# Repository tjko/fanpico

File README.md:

# Fanpico: Programmable PWM (PC) Fan Controller

<p></p>

Fanpico is a smart PWM (PC) fan controller based around [Raspberry Pi Pico](https://www.raspberrypi.com/documentation/microcontrollers/raspberry-pi-pico.html) (RP2040 MCU). Fanpico operates as standalone controller that can be configured and left running. It does not require any drivers and doesn't care what OS is being used. FanPico is an Open-source hardware (OSHW) project.

## What is it for?
* Fanpico is for customizing fan "curves" to fine tune how your motherboard controlled fans run.
* Fine tuning fan speeds to easily balance airflow.
* Controlling fan based on temperature sensor input.
* Monitoring fan speeds and behaviour as well as monitoring what exactly motherboard is doing.
* Fanpico works also as standalong controller for other things than a PC, it's been used  controlling fans on 3D printers and on enclosed network equipment racks, etc..

## Features
* Controls up to 8 fans.
* Connect up to 4 motherboard fan outputs.
* Connect up to 2 remote temperature probes (plus onboard "ambient" temperature sensor).
* Support for [1-Wire Temperature sensors](https://github.com/tjko/fanpico/wiki/1%E2%80%90Wire-Temperature-Sensors-with-FanPico) (up to 8 sensors)
* Support for [I2C Temperature sensors](https://github.com/tjko/fanpico/wiki/I2C-Temperature-Sensors-with-FanPico) (up to 8 sensors)
* [OLED](https://github.com/tjko/fanpico/wiki/OLED-(I2C)-Display-Support) and [LCD](https://github.com/tjko/fanpico/wiki/LCD-(SPI)-Panel-Connection) display support (boards where model name ends with "D").
* Can be powered from motherboard fan outputs or using auxiliary power connector (4-Pin Floppy or DC Barrel jack connector).
* Ability to define custom fan "curves" for each fan.
* Ability to provide custom tachometer (fan RPM) output signal back to motherboard.
* Support for Locked Rotor (Alarm) signal fans (allows using regular tachometer fans with system expecting Locked Rotor Alarm fans and vice versa).
* Control fans from any motherboard PWM signal or from temperature sensors.
* OS Independent, no drivers or software needed.
* Configuration stored on the device itself (in the flash memory).
* SCPI "like" programming interface (see [Command Reference](commands.md))
* Monitor each fan and motherboard output signals as well as temperatures.
* [WiFi support](https://github.com/tjko/fanpico/wiki/FanPico-Network-Interface) if opting to mount Pico W on the board.
  * [HTTP server](https://github.com/tjko/fanpico/wiki/Fanpico-HTTP-Server) with TLS (HTTPS) support.
  * [MQTT client](https://github.com/tjko/fanpico/wiki/FanPico-MQTT-Tutorial) with TLS support for logging data and to receive commands.
  * [Home Assistant](https://github.com/tjko/fanpico/wiki/FanPico-Home-Assistant-(MQTT-Discovery)-Support) support using MQTT Discovery feature.
  * Telnet server for configuration and monitoring.
  * [SSH server](https://github.com/tjko/fanpico/wiki/Fanpico-Using-SSH-Server) for configuration and monitoring (experimental).
  * [SNMP Agent](https://github.com/tjko/fanpico/wiki/SNMP-Agent-Usage) for monitoring.

### Interfaces

* Serial "Console". Primary method for configuring/monitoring FanPico units is via (USB) Serial console (some units also have 3.3V TTL Serial connection).
* Desktop application (that polls FanPico using SCPI commands over the console connection): [FanPico Monitor](https://github.com/tjko/fanpico-monitor)
* Web Interface (available when using _Pico W_) over WiFi

For more documentation check [FanPico Wiki](https://github.com/tjko/fanpico/wiki)

## Sponsors
I would like to thank following sponsors, who have helped FanPico project:

* PCBWay

## Where can I get one?
Currently Fanpico is available as a DIY project.
Check discussion forums for places to purchase Kits or PCBs: [Places to Purchase FanPico](https://github.com/tjko/fanpico/discussions/12)

(Instructions for building the kit are in [FanPico Wiki](https://github.com/tjko/fanpico/wiki))

However, if there is sufficient interest, then ready-made units may be made available for sale.
If you'd be interested in purchasing FanPico pease indicate your interest here: [FanPico Forum](https://github.com/tjko/fanpico/discussions/9)

### DIY Option
You can upload the Kerber files (found under boards directory) to your favorite PCB maker website and get your boards produced in matter of days.
Component list (BOM or bill of materials) is found under boards directory as well along with the electrical schematics.

NOTE, check [discussions forum](https://github.com/tjko/fanpico/discussions/) for giveaways for free PCBs.

### Review Units
If you are member of press (or YouTuber) and would like to review/test Fanpico. Please contact me via email.

## How Can I help?
* Build your own FanPico and provide feedback, suggestions (see discussion forums).
* If you're into electronics new/improved board designs are most welcome.
* If you're into programming:
  - Create cool (desktop) program that allows easily configuring FanPico boards (with ability to "draw" fan curves, etc..) and to monitor Fan statuses.
  - Help improve the firmware.
* If you're into graphics (or web) design:
  - Help create cool (but lightweight) web interface
  - Create better logo for FanPico
* As this is Open (Source) Hardware Project, if you like to build (and sell) assembled boards or DIY kits, you'd be most welcome...
* You can always donate (and get your name added to the Sponsors section, if you so wish).

## Hardware
Fanpico is Open Source Hardware, reference design is provided for the "0804" model (8 fan outputs and 4 motherboard fan inputs), and "0804D" model that adds OLED display support (hence the "D" suffix).

Additional models with different combinations of fan inputs/outputs could be easily designed (takining into account limitations of Raspberry Pi Pico I/O limits). New and improved PCB models/designs are most welcome.

Model "0840D" with (with right-angle connectors and DC power connector):

Model "0804" without display (with straight connectors):

### Hardware Design
Fanpico (reference design) utilizes all available I/O pins on a Raspberry Pi Pico.
* Fan PWM outputs are driven by the Pico's PWM hardware.
* Motherboard Fan PWM inputs are read using Pico's PWM hardware.
* Tacho signal output (for motherboard connectors) is generated using Pico's PIO hardware, providing extremely stable tachometer signal.
* Tacho signal inputs (from fans) are read differently in model 0804 and 0804D:
  - 0804: signals are read using GPIO interrupts, measuring all fans simultaneously by counting number of pulses received over a period of time.
  - 0804D: signals are read through multiplexer measuring one fan at a time, by measuring pulse length.
* Temperature readings are done using ADC, with help of a accurrate 3V voltage reference (LM4040). Any NTC (10k or 100k) thermistors can be used as themperature sensors.
* Each FAN output has jumper to select whether fan gets its power from associated MBFAN connector or from the AUX connector
* There is a jumper to select whether power the Fanpico itself from MBFAN1 or AUX connector.

To help design and test Fanpico couple other projects were born:
* [Tiny PicoProbe](https://github.com/tjko/tiny-picoprobe/) - tiny PicoProbe implementation.
* [Fan Test Adapter](https://github.com/tjko/fan-test-adapter/) - adapter to help simulate motherboard fan outputs.

Projects based on FanPico firmware:
* [BrickPico](https://github.com/tjko/brickpico/) - (LEGO) LED Light Kit Controller.

### Models (PCB designs)
Currently following models are available:

|Model|Fans (Outputs)|MB Fan (Inputs)|External Temperature Sensors|Display|Notes|
|-----|--------------|---------------|-------------------|--------|-----|
|[FANPICO-0804](boards/fanpico-0804/)|8|4|2|N|First publicly available board (reference design).|
|[FANPICO-0804D](boards/fanpico-0804D/)|8|4|2|Y|Support for OLED (128x64 or 128x128) displays|
|[FANPICO-0401D](boards/fanpico-0401D/)|4|1|2|Y|Adds QWIIC and 1-Wire connectors.|
|[FANPICO-0200](boards/fanpico-0200/)|2|0|2|Y|OLED display supported via QWIIC connector. PCB under development.

(all boards have one additional 'on-board' temperature sensor on the RP2040 MCU itself)

Models ending with "D" have connector to attach OLED display module to see 'real-time' status of fans and temperatures.

OLED panel directly mounted on the PCB:

LCD Panel attached via a short cable:

#### Accessory Boards (PCB designs)
Following accessories are available:

|Model|Info|
|-----|----|
|[OLED-Adapter](boards/oled-adapter/)|Mounting adapter for OLED boards with different pinouts.|
|[Power-Board](boards/power-board/)|Adapter for using high-power fans with FanPico.|

## Firmware
Firmware is developed in C using the Pico SDK. Pre-compiled firmware is released when there is new major features or bug fixes.

Latest pre-compiled firmware image can be found here: [Releases](https://github.com/tjko/fanpico/releases)

To get latest firmware with latest updates/fixes you must compile the firmware from the sources.

### Installing firmware image
Firmware can be installed via the built-in UF2 bootloader on the Raspberry Pi Pico or using the debug header with Picoprobe, etc...

#### Selecting Right Firmware to use
Each release (zip file) contains multiple different firmware files.
Make sure to select firmware for the board you're using and for the pico model ("pico_w" if using Pico W).

Firmware file names have format: fanpico-<board_model>-<pico_model>.uf2
```
fanpico-0401D-pico.uf2
fanpico-0401D-pico_w.uf2
fanpico-0804-pico.uf2
fanpico-0804-pico_w.uf2
fanpico-0804D-pico.uf2
fanpico-0804D-pico_w.uf2
```

#### Upgrading Firmware
Firmware upgrade steps:
* Boot Pico into UF2 bootloader. This can be done in two ways:
  1)  Press and hold "bootsel" button and then press and release "reset" button.
  2)  Issue command: SYS:UPGRADE
* Copy firmware file to the USB mass storage device that appears.
* As soon as firmware copy is complete, Pico will reboot and run the fanpico firmware.

### Building Firmware Images

Raspberry Pi Pico C/C++ SDK is required for compiling the firmware:

#### Requirements / Dependencies
* [Raspberry Pi Pico C/C++ SDK](https://www.raspberrypi.com/documentation/microcontrollers/c_sdk.html)
* [cJSON](https://github.com/DaveGamble/cJSON)
* [pico-lfs](https://github.com/tjko/pico-lfs)
* [ss_oled-lib](https://github.com/tjko/ss_oled-lib)
* [bb_spi_lcd-lib](https://github.com/tjko/bb_spi_lcd-lib)
* [libb64](https://github.com/libb64/libb64)
* [pico-telnetd](https://github.com/tjko/pico-telnetd)
* [pico-1wire-lib](https://github.com/tjko/pico-1wire-lib)
* [pico-sensor-lib](https://github.com/tjko/pico-sensor-lib)
* [wolfSSL](https://github.com/wolfSSL/wolfssl)
* [wolfSSH](https://github.com/wolfSSL/wolfssh)
* [pico-sshd](https://github.com/tjko/pico-sshd)

##### Install Pico SDK
Pico SDK must be installed working before you can compile fanpico.

Instructions on installing Pico SDK see: [Getting started with Raspberry Pi Pico](https://datasheets.raspberrypi.com/pico/getting-started-with-pico.pdf)

(Make sure PICO_SDK_PATH environment variable is set)

##### Downloading sources

Create some directory for building fanpico ('src' used in this example):
```
$ mkdir src
$ cd src
$ git clone https://github.com/tjko/fanpico.git
$ git submodule update --init --recursive
```

##### Building fanpico firmware

To build fanpico firmware, first create a build directory:
```
$ cd fanpico
$ mkdir build
```

Select which board to build firmware for (default is "0804") and which Pico is to be used (default is "pico"):
```
$ cd build
$ cmake -DFANPICO_BOARD=0804D -DPICO_BOARD=pico_w ..
```

Then compile fanpico:
```
$ make -j
```

After successful compile you should see firmware binary in the build directory:
subdirectory:

```
$ ls *.uf2
fanpico.uf2
```

If you have picotool installed you can check the firmware image information:
```
$ picotool info -a fanpico.uf2
File fanpico.uf2 family ID 'rp2040':

Program Information
 name:              fanpico
 version:           1.7.6
 web site:          https://kokkonen.net/fanpico/
 description:       FanPico-0804D - Smart PWM Fan Controller
 features:          USB stdin / stdout
 boot settings:     bootdelay = 0
                    safemode = 0
 binary start:      0x10000000
 binary end:        0x1012edc0
 embedded drive:    0x101c0000-0x10200000 (256K): littlefs

Fixed Pin Information
 0:                 TX (Serial) / MISO (SPI)
 1:                 RX (Serial) / CS (SPI)
 2:                 SDA (I2C) / SCK (SPI)
 3:                 SCL (I2C) / MOSI (SPI)
 4:                 Fan1 PWM signal (output)
 5:                 Fan2 PWM signal (output)
 6:                 Fan3 PWM signal (output)
 7:                 Fan4 PWM signal (output)
 8:                 Fan5 PWM signal (output)
 9:                 Fan6 PWM signal (output)
 10:                Fan7 PWM signal (output)
 11:                Fan8 PWM signal (output)
 12:                MB Fan1 tacho signal (output)
 13:                MB Fan1 PWM signal (input)
 14:                MB Fan2 tacho signal (output)
 15:                MB Fan2 PWM signal (input)
 16:                MB Fan3 tacho signal (output)
 17:                MB Fan3 PWM signal (input)
 18:                MB Fan4 tacho signal (output)
 19:                MB Fan4 PWM signal (input)
 20:                Multiplexer S2 (output)
 21:                Multiplexer S1 (output)
 22:                Multiplexer S0 (output)
 26:                Multiplexer A [tacho signal] (input)
 27:                Temperature Sensor1 (input)
 28:                Temperature Sensor2 (input)

Build Information
 sdk version:       2.1.1
 pico_board:        pico_w
 boot2_name:        boot2_w25q080
 build date:        Jul 10 2025
 build attributes:  Release

Metadata Blocks
 none
```

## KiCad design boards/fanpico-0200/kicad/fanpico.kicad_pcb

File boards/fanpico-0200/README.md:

# FANPICO-0200 PCB

PCB Size: 81.0mm x 60.0mm

## Change Log

v1.1
- Add fuse (F3) to prevent pulling too much current through the buck regulator.
- Move sensor connectors footprints (J16 & J17) slightly away from board edge
  to allow better fitment of right angle connectors.

v1.0
- First Prototye

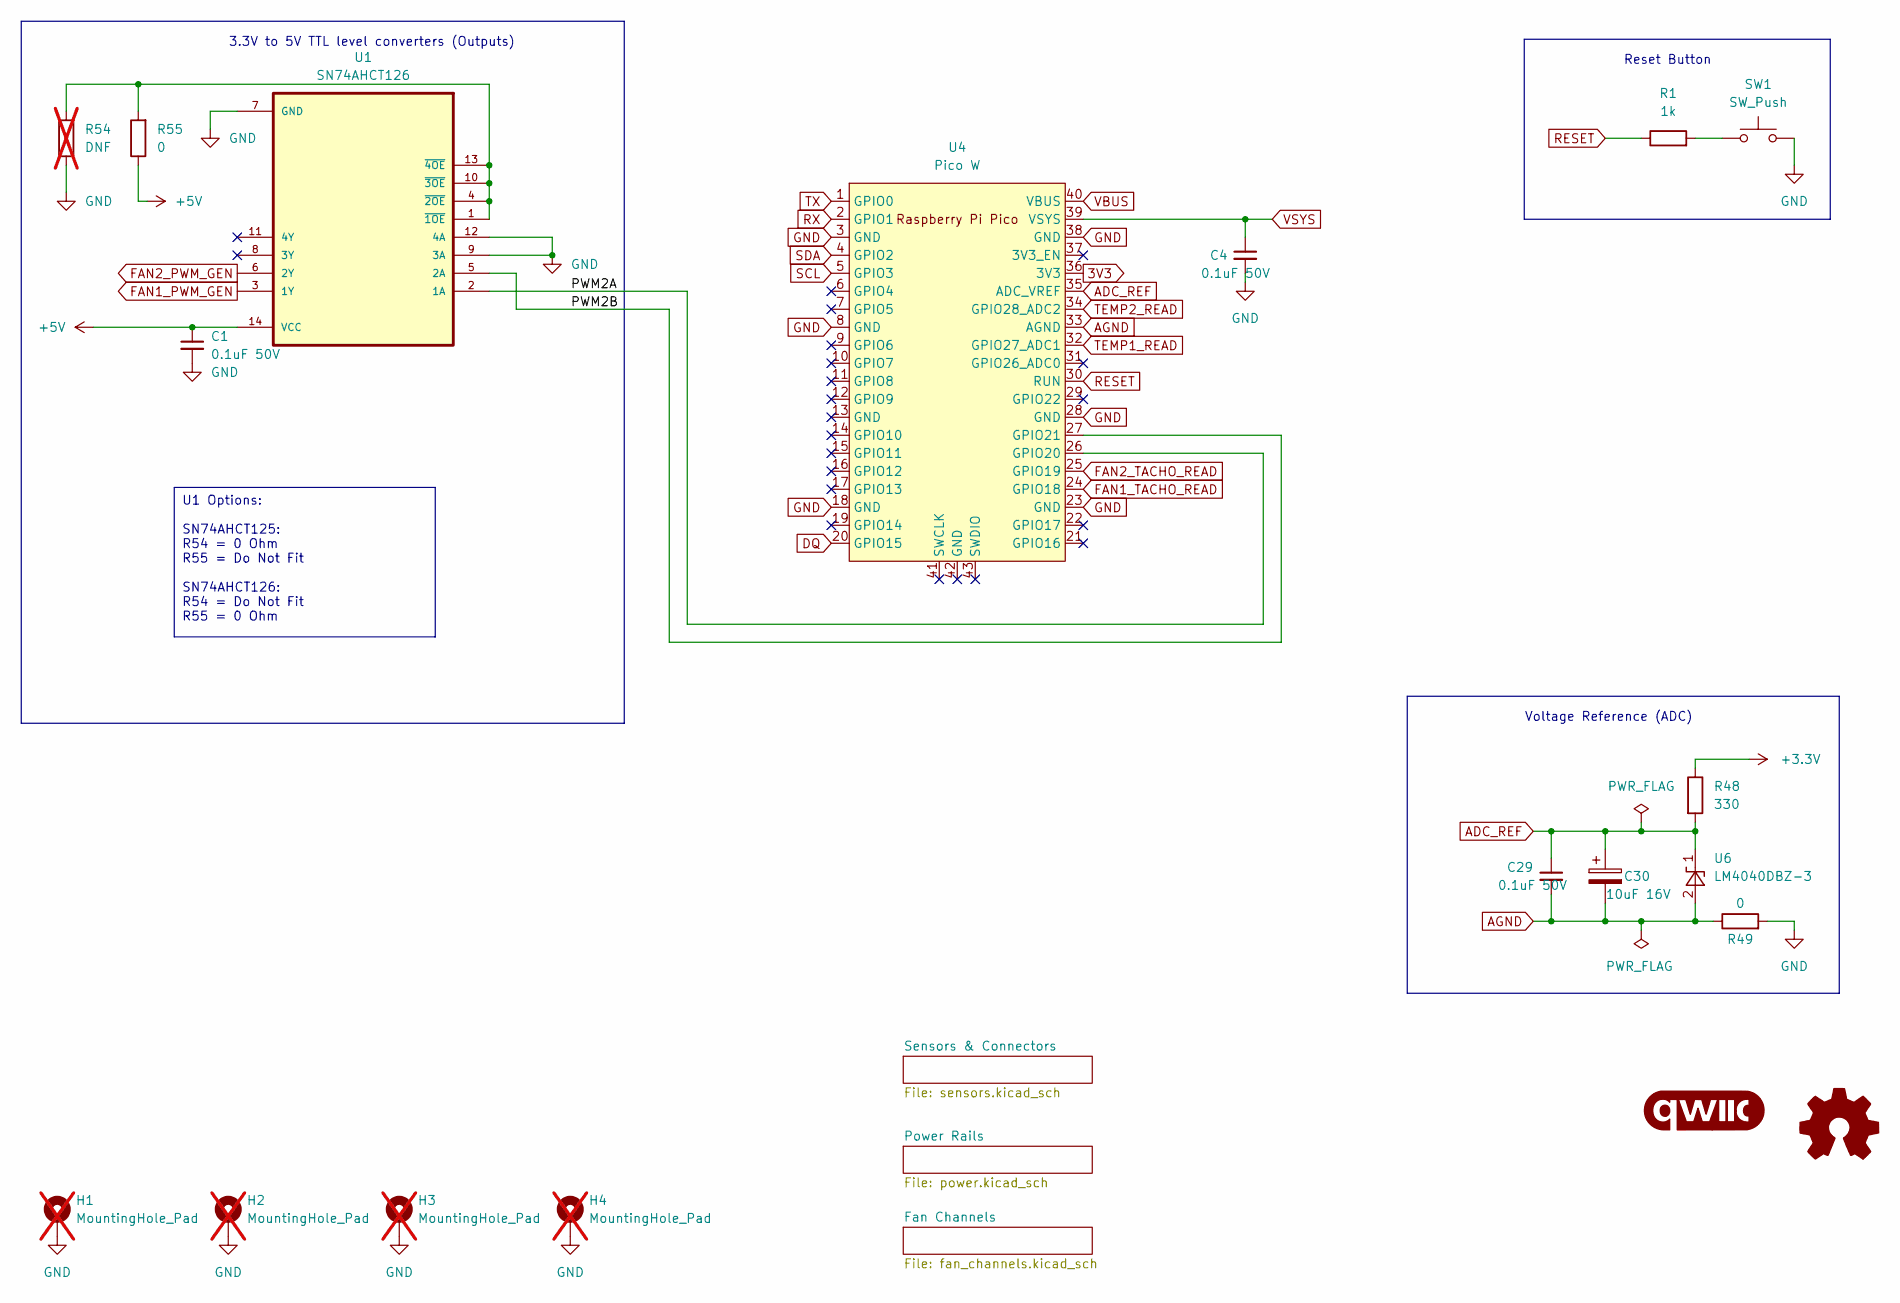
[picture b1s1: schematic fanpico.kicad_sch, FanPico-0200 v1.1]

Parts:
C1, C4, C29: 0.1uF 50V; C_0603_1608Metric_Pad1.08x0.95mm_HandSolder; Manufacturer Part Number CL10B104KB8NNNC; LCSC Part Number C1591
C30: 10uF 16V; CP_EIA-3216-18_Kemet-A_Pad1.58x1.35mm_HandSolder; Mouser Part Number 80--T491A106K016; LCSC Part Number C7171
G1: qwiic_Logo; qwiic_5mm
G2: Logo_Open_Hardware_Small; OSHW-Logo_5.7x6mm_SilkScreen
H1, H2, H3, H4: MountingHole_Pad; MountingHole_3.2mm_M3_Pad_Via; not fitted
R1: 1k; R_0603_1608Metric_Pad0.98x0.95mm_HandSolder; Manufacturer Part Number RC0603FR-071KL; LCSC Part Number C22548
R48: 330; R_0603_1608Metric_Pad0.98x0.95mm_HandSolder; Manufacturer Part Number RC0603FR-07330RL; LCSC Part Number C105881
R49, R55: 0; R_0603_1608Metric_Pad0.98x0.95mm_HandSolder; Manufacturer Part Number 0603WAF0000T5E; LCSC Part Number C21189
R54: DNF; R_0603_1608Metric_Pad0.98x0.95mm_HandSolder; Manufacturer Part Number 0603WAF0000T5E; LCSC Part Number C21189; not fitted
SW1: SW_Push; SW-SMD_L3.9-W3.0-P4.45; Manufacturer Part Number TS-1088-AR02016; LCSC Part Number C720477
U1: SN74AHCT126; TSSOP-14_4.4x5mm_P0.65mm; Manufacturer Part Number SN74AHCT126PWR; LCSC Part Number C155177
U4: Pico W; RPi_Pico_PicoW_SMD_TH; Manufacturer Part Number Pico W / Pico 2 W
U6: LM4040DBZ-3; SOT-23; Manufacturer Part Number LM4040AIM3-3.0+T; LCSC Part Number C143326

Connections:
3V3: R48.1, U4.36 (3V3); also elsewhere on the board
+5V: C1.1, R55.1, U1.14 (VCC); also elsewhere on the board
/PWM2A: U1.2 (1A), U4.26 (GPIO20)
/PWM2B: U1.5 (2A), U4.27 (GPIO21)
ADC_REF: C29.1, C30.1, R48.2, U4.35 (ADC_VREF), U6.1 (K); also elsewhere on the board
AGND: C29.2, C30.2, R49.1, U4.33 (AGND), U6.2 (A); also elsewhere on the board
DQ: U4.20 (GPIO15); also elsewhere on the board
FAN1_PWM_GEN: U1.3 (1Y); also elsewhere on the board
FAN1_TACHO_READ: U4.24 (GPIO18); also elsewhere on the board
FAN2_PWM_GEN: U1.6 (2Y); also elsewhere on the board
FAN2_TACHO_READ: U4.25 (GPIO19); also elsewhere on the board
GND: C1.2, C4.2, H1.1, H2.1, H3.1, H4.1, R49.2, R54.1, SW1.2, U1.7 (GND), U1.9 (3A), U1.12 (4A), U4.3 (GND), U4.8 (GND), U4.18 (GND), U4.23 (GND), U4.28 (GND), U4.38 (GND); also elsewhere on the board
unnamed: R1.2, SW1.1
unnamed: R54.2, R55.2, U1.1 (~1OE), U1.4 (~2OE), U1.10 (~3OE), U1.13 (~4OE)
RESET: R1.1, U4.30 (RUN)
RX: U4.2 (GPIO1); also elsewhere on the board
SCL: U4.5 (GPIO3); also elsewhere on the board
SDA: U4.4 (GPIO2); also elsewhere on the board
TEMP1_READ: U4.32 (GPIO27_ADC1); also elsewhere on the board
TEMP2_READ: U4.34 (GPIO28_ADC2); also elsewhere on the board
TX: U4.1 (GPIO0); also elsewhere on the board
VBUS: U4.40 (VBUS); also elsewhere on the board
VSYS: C4.1, U4.39 (VSYS); also elsewhere on the board

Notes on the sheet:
U1 Options: SN74AHCT125: R54 = 0 Ohm R55 = Do Not Fit SN74AHCT126: R54 = Do Not Fit R55 = 0 Ohm
Reset Button
3.3V to 5V TTL level converters (Outputs)
Voltage Reference (ADC)

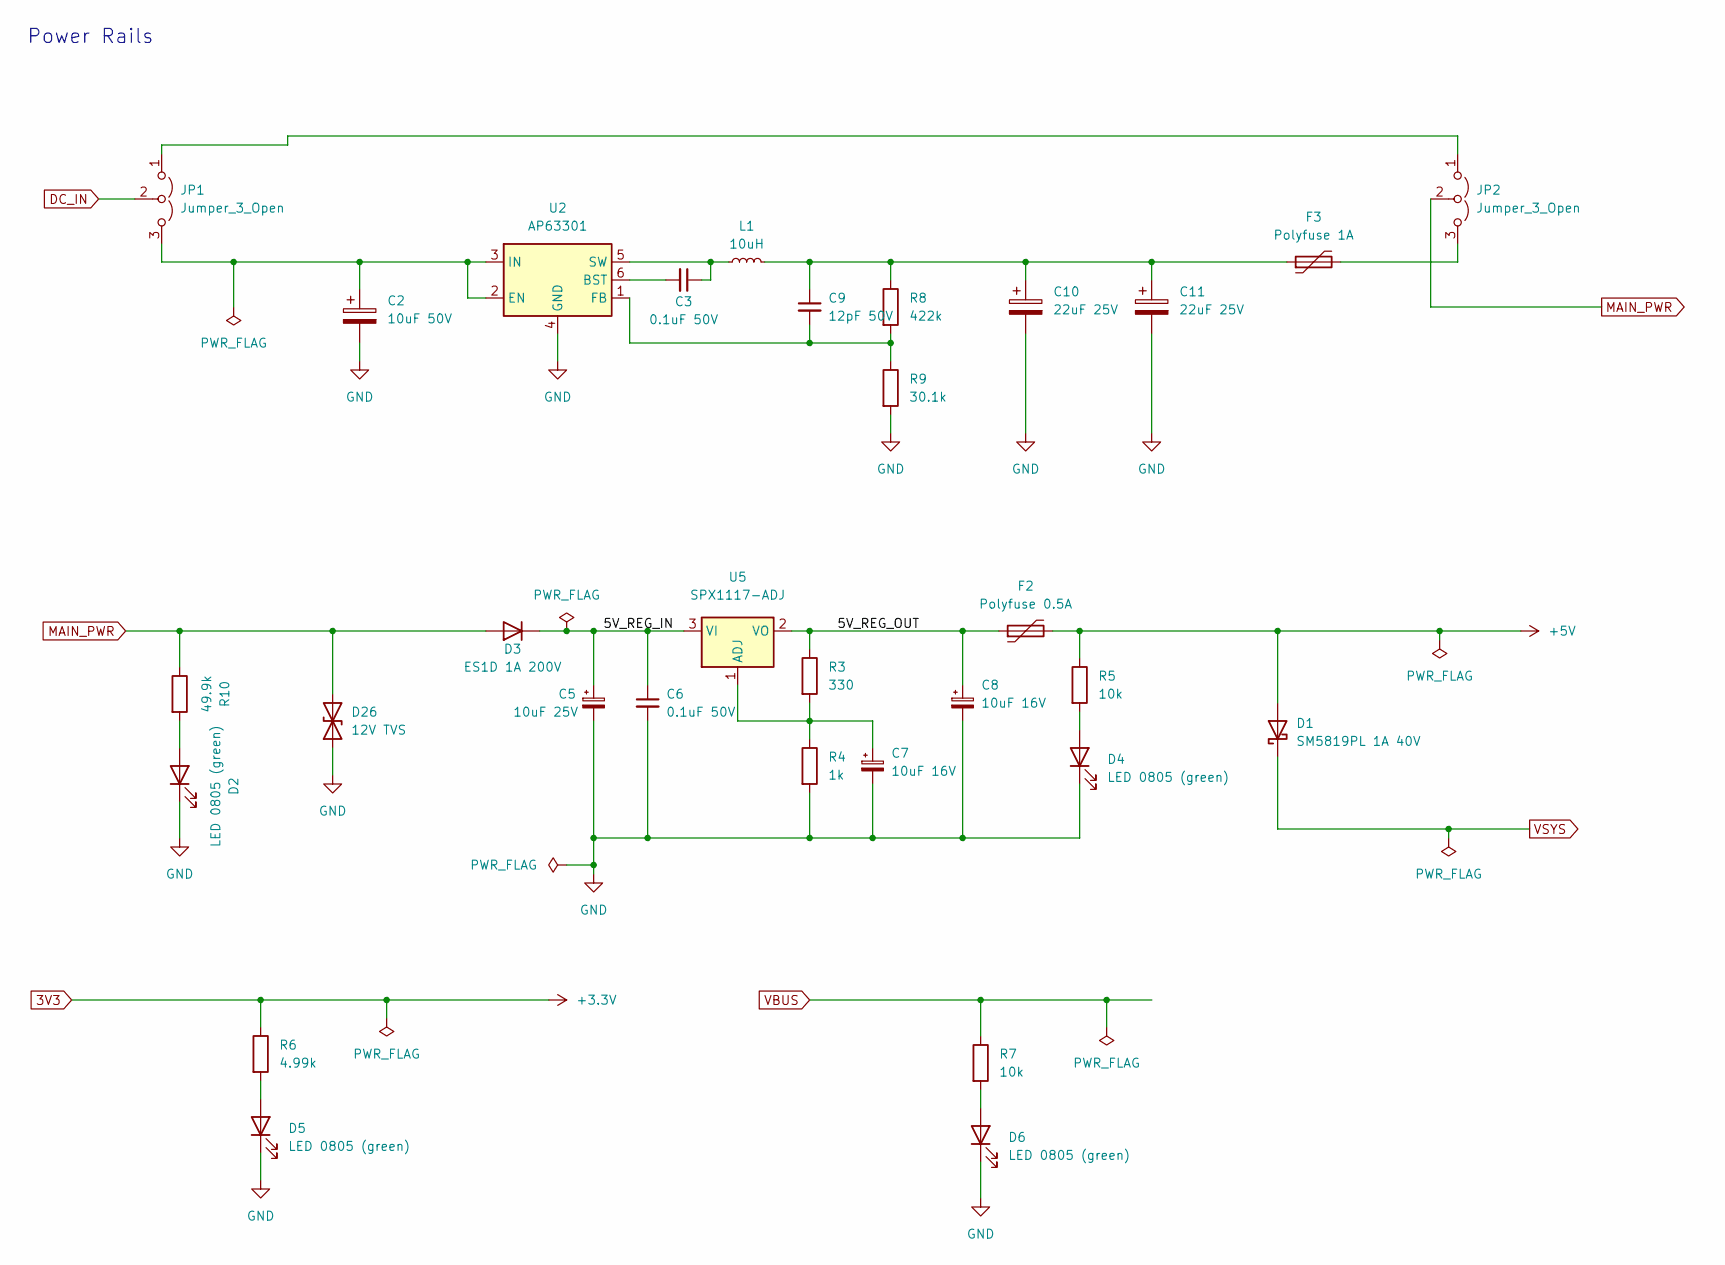
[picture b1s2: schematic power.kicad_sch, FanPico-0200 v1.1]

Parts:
C2: 10uF 50V; CP_EIA-3216-18_Kemet-A_Pad1.58x1.35mm_HandSolder; Manufacturer Part Number CL31B106KBHNNNE; LCSC Part Number C89632
C3, C6: 0.1uF 50V; C_0603_1608Metric_Pad1.08x0.95mm_HandSolder; Manufacturer Part Number CL10B104KB8NNNC; LCSC Part Number C1591
C5: 10uF 25V; CP_EIA-3528-12_Kemet-T_Pad1.50x2.35mm_HandSolder; Manufacturer Part Number TAJB106K025RNJ; LCSC Part Number C7194
C7, C8: 10uF 16V; CP_EIA-3216-18_Kemet-A_Pad1.58x1.35mm_HandSolder; Mouser Part Number 80--T491A106K016; LCSC Part Number C7171
C9: 12pF 50V; C_0603_1608Metric_Pad1.08x0.95mm_HandSolder; Manufacturer Part Number CL10C120JB8NNNC; LCSC Part Number C38523
C10, C11: 22uF 25V; CP_EIA-3216-18_Kemet-A_Pad1.58x1.35mm_HandSolder; Manufacturer Part Number CL31A226KAHNNNE; LCSC Part Number C12891
D1: SM5819PL 1A 40V; D_SMA; Mouser Part Number 833-SM5819PL-TP; LCSC Part Number C669023
D2, D4, D5, D6: LED 0805 (green); LED_0805_2012Metric_Pad1.15x1.40mm_HandSolder; Mouser Part Number 710-150080GS75000; LCSC Part Number C434432
D3: ES1D 1A 200V; D_SMA_Handsoldering; Mouser Part Number 512-ES1D; LCSC Part Number C445494
D26: 12V TVS; D_SOD-323_HandSoldering; Manufacturer Part Number UDD32C12L01-ES; LCSC Part Number C5199168
F2: Polyfuse 0.5A; Fuse_1206_3216Metric_Pad1.42x1.75mm_HandSolder; Mouser Part Number 530-0ZCJ0050AF2E; LCSC Part Number C70072
F3: Polyfuse 1A; Fuse_1206_3216Metric_Pad1.42x1.75mm_HandSolder; Manufacturer Part Number 1206L100/30NR; LCSC Part Number C7542958
JP1, JP2: Jumper_3_Open; PinHeader_1x03_P2.54mm_Vertical; Manufacturer Part Number PZ254V-11-03P; LCSC Part Number C2937625
L1: 10uH; IND-SMD_L7.2-W6.6_GPSR07X0; Manufacturer Part Number CYA0630-10UH; LCSC Part Number C5189958
R3: 330; R_0603_1608Metric_Pad0.98x0.95mm_HandSolder; Manufacturer Part Number RC0603FR-07330RL; LCSC Part Number C105881
R4: 1k; R_0603_1608Metric_Pad0.98x0.95mm_HandSolder; Manufacturer Part Number RC0603FR-071KL; LCSC Part Number C22548
R5, R7: 10k; R_0603_1608Metric_Pad0.98x0.95mm_HandSolder; Manufacturer Part Number RC0603FR-0710KL; LCSC Part Number C98220
R6: 4.99k; R_0603_1608Metric_Pad0.98x0.95mm_HandSolder; Manufacturer Part Number RC0603FR-074K99L; LCSC Part Number C114621
R8: 422k; R_0603_1608Metric_Pad0.98x0.95mm_HandSolder; Manufacturer Part Number RC0603FR-07422KL; LCSC Part Number C245966
R9: 30.1k; R_0603_1608Metric_Pad0.98x0.95mm_HandSolder; Manufacturer Part Number 0603WAF3012T5E; LCSC Part Number C23000
R10: 49.9k; R_0603_1608Metric_Pad0.98x0.95mm_HandSolder; Manufacturer Part Number RC0603FR-0749K9L; LCSC Part Number C114624
U2: AP63301; TSOT-26; Manufacturer Part Number AP63301WU-7; LCSC Part Number C2158003
U5: SPX1117-ADJ; SOT-223-3_TabPin2; Manufacturer Part Number SPX1117M3-L/TR; LCSC Part Number C67402

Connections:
3V3: R6.1; also elsewhere on the board
+5V: D1.2 (A), F2.2, R5.1; also elsewhere on the board
/Power Rails/5V_REG_IN: C5.1, C6.1, D3.1 (K), U5.3 (VI)
/Power Rails/5V_REG_OUT: C8.1, F2.1, R3.1, U5.2 (VO)
DC_IN: JP1.2 (C); also elsewhere on the board
GND: C2.2, C5.2, C6.2, C7.2, C8.2, C10.2, C11.2, D2.1 (K), D4.1 (K), D5.1 (K), D6.1 (K), D26.1 (A1), R4.2, R9.2, U2.4 (GND); also elsewhere on the board
MAIN_PWR: D3.2 (A), D26.2 (A2), JP2.2 (C), R10.1; also elsewhere on the board
unnamed: C9.1, C10.1, C11.1, F3.1, L1.2, R8.1
unnamed: D2.2 (A), R10.2
unnamed: D4.2 (A), R5.2
unnamed: D5.2 (A), R6.2
unnamed: D6.2 (A), R7.2
unnamed: JP1.1 (A), JP2.1 (A)
unnamed: C2.1, JP1.3 (B), U2.2 (EN), U2.3 (IN)
unnamed: F3.2, JP2.3 (B)
unnamed: C3.2, U2.6 (BST)
unnamed: C9.2, R8.2, R9.1, U2.1 (FB)
unnamed: C3.1, L1.1, U2.5 (SW)
unnamed: C7.1, R3.2, R4.1, U5.1 (ADJ)
VBUS: R7.1; also elsewhere on the board
VSYS: D1.1 (K); also elsewhere on the board

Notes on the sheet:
Power Rails

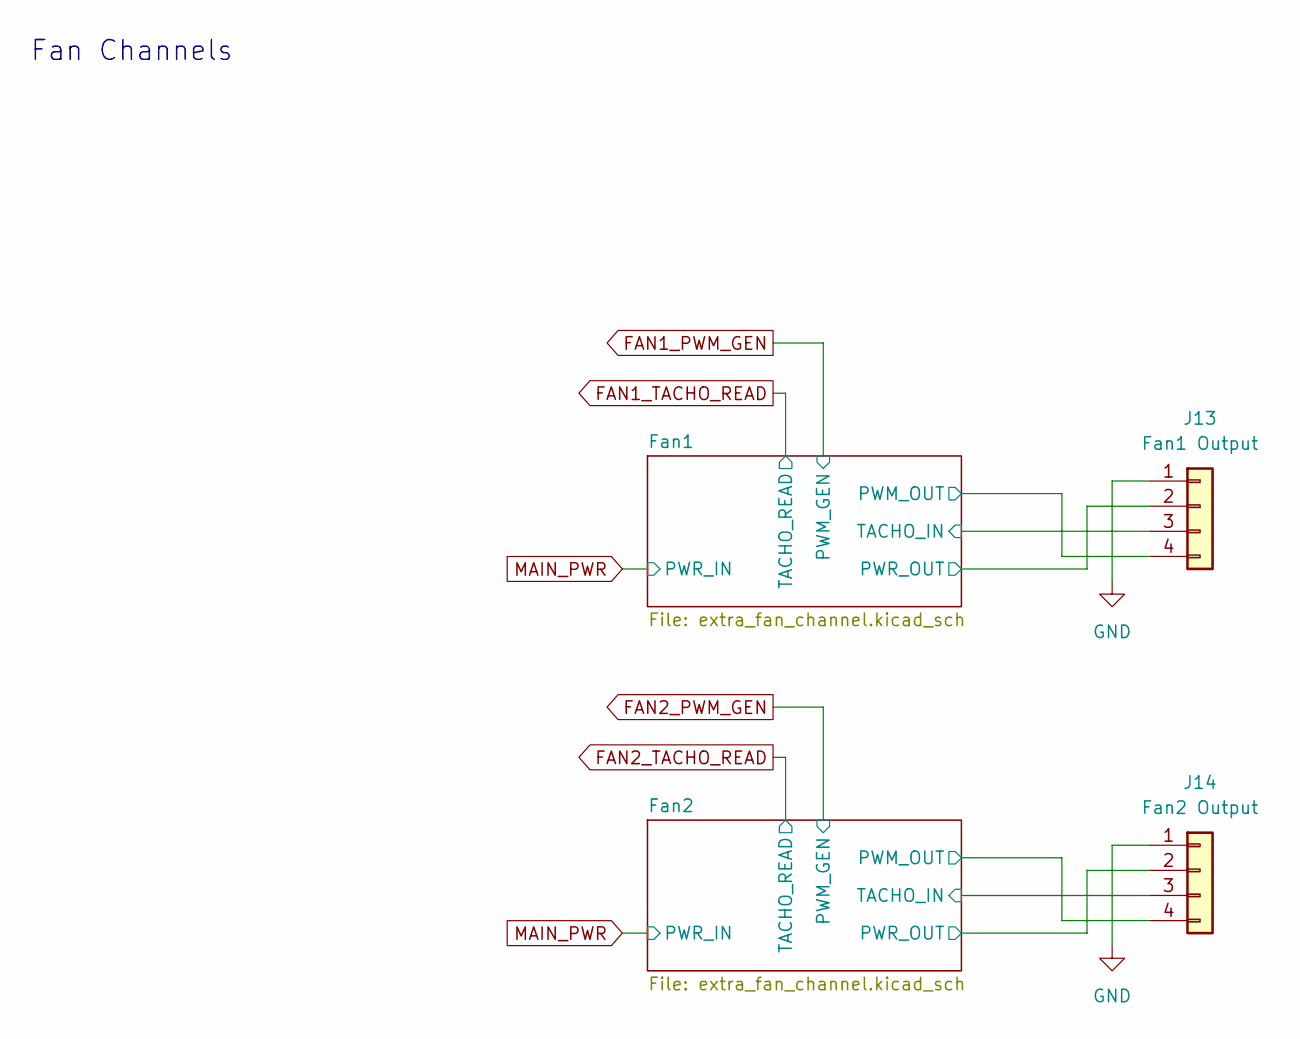
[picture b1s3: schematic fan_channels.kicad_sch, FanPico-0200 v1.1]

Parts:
J13: Fan1 Output; FanPinHeader_1x04_P2.54mm_Vertical; Mouser Part Number 538-47053-1000; LCSC Part Number C240840
J14: Fan2 Output; FanPinHeader_1x04_P2.54mm_Vertical; Mouser Part Number 538-47053-1000; LCSC Part Number C240840

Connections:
/Fan Channels/Fan1/PWM_OUT: J13.4; also elsewhere on the board
/Fan Channels/Fan1/TACHO_IN: J13.3; also elsewhere on the board
/Fan Channels/Fan2/PWM_OUT: J14.4; also elsewhere on the board
/Fan Channels/Fan2/TACHO_IN: J14.3; also elsewhere on the board
GND: J13.1, J14.1; also elsewhere on the board
MAIN_PWR: J13.2, J14.2; also elsewhere on the board

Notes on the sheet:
Fan Channels

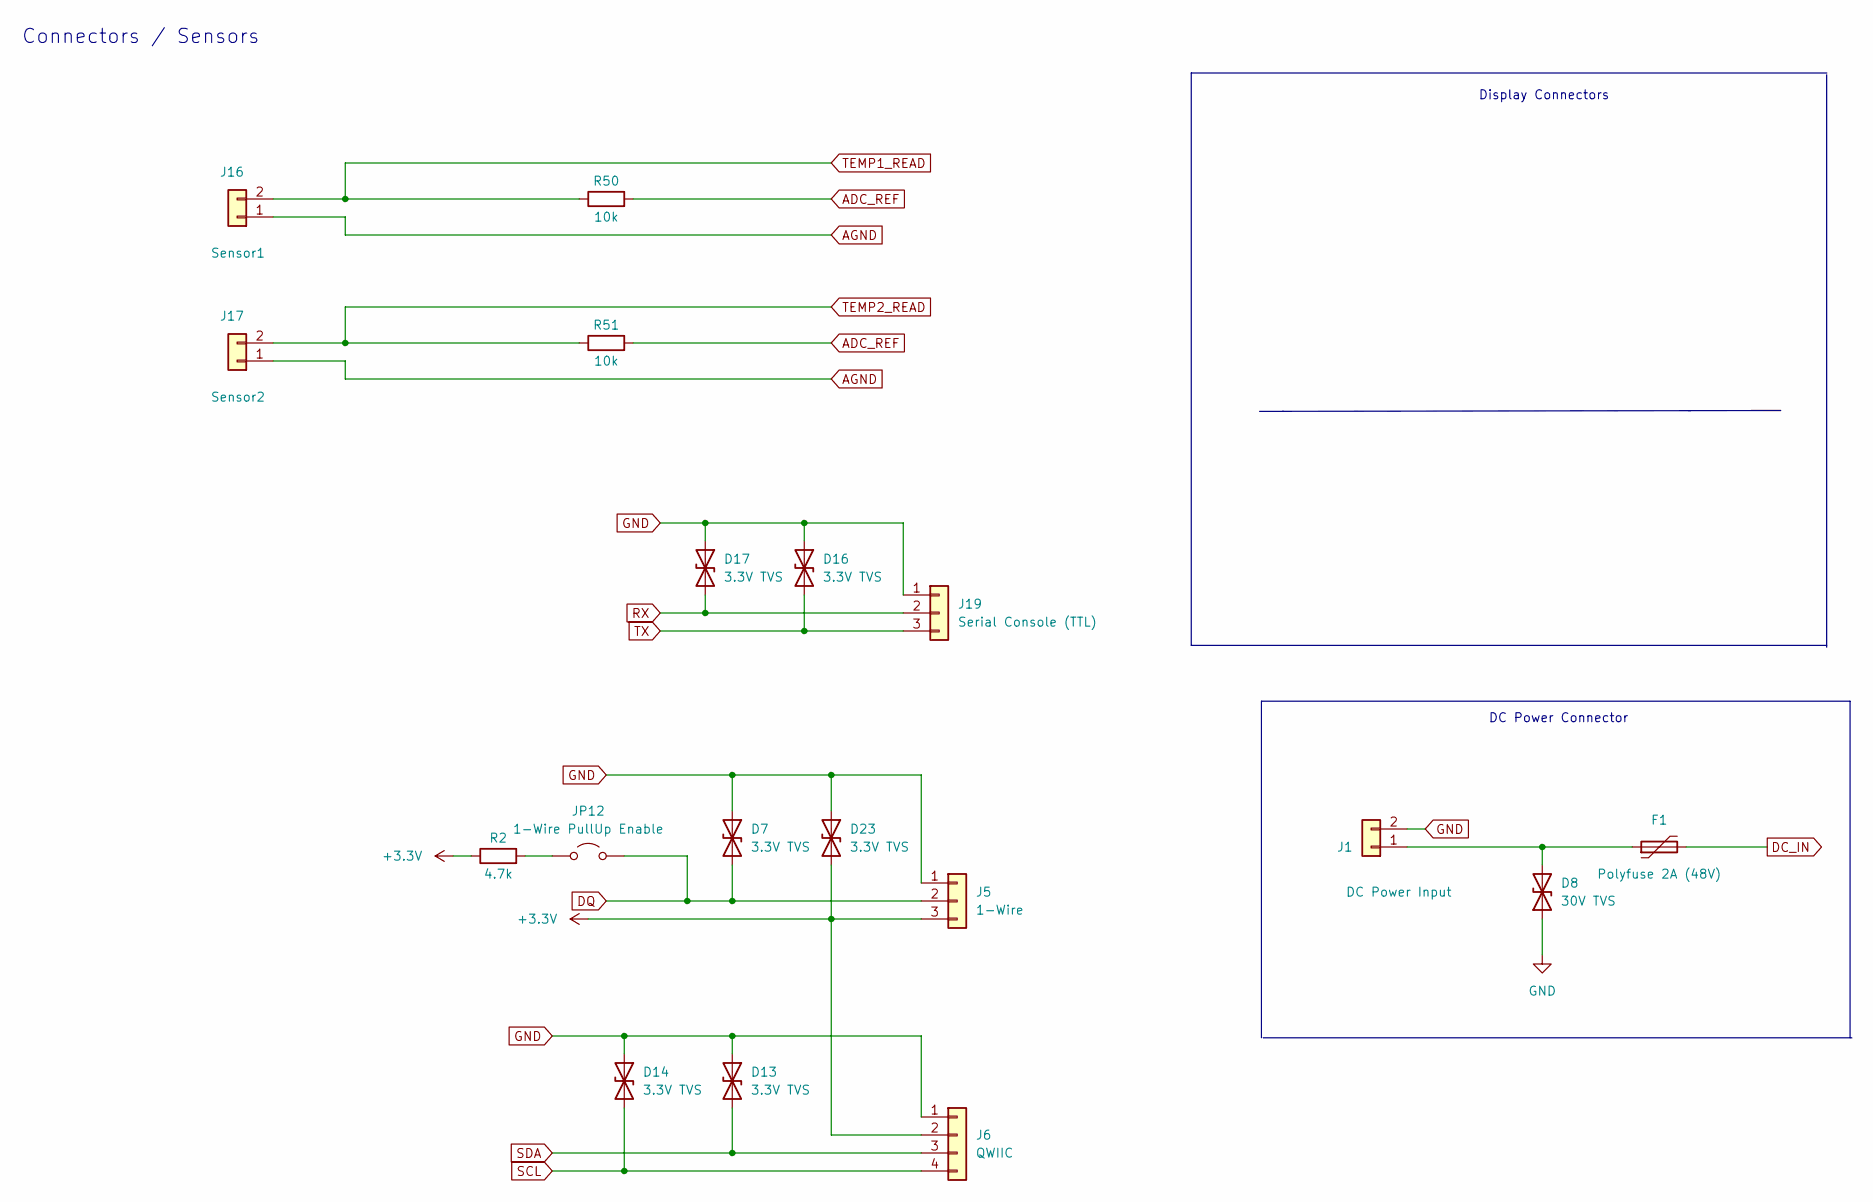
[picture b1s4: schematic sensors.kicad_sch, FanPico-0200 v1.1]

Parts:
D7, D13, D14, D16, D17, D23: 3.3V TVS; D_SOD-323_HandSoldering; Manufacturer Part Number UDD32C03L01; LCSC Part Number C78439
D8: 30V TVS; D_0603_1608Metric_Pad1.05x0.95mm_HandSolder; Manufacturer Part Number PESD0603MS30-MS; LCSC Part Number C7473181
F1: Polyfuse 2A (48V); Fuse_2920_7451Metric_Pad2.10x5.45mm_HandSolder; Manufacturer Part Number BSMD2920-200-48V; LCSC Part Number C22399926
J1: DC Power Input; TerminalBlock_Phoenix_MKDS-1,5-2_1x02_P5.00mm_Horizontal; Mouser Part Number 651-1715022; LCSC Part Number C1509679
J5: 1-Wire; TerminalBlock_TE_282834-3_1x03_P2.54mm_Horizontal; Manufacturer Part Number 2.54-3P; LCSC Part Number C68305
J6: QWIIC; JST_SH_SM04B-SRSS-TB_1x04-1MP_P1.00mm_Horizontal; Manufacturer Part Number SM04B-SRSS-TB(LF)(SN); LCSC Part Number C160404
J16: Sensor1; JST_XH_B2B-XH-A_1x02_P2.50mm_Vertical; Manufacturer Part Number XH-2A; LCSC Part Number C20079
J17: Sensor2; JST_XH_B2B-XH-A_1x02_P2.50mm_Vertical; Manufacturer Part Number XH-2A; LCSC Part Number C20079
J19: Serial Console (TTL); PinHeader_1x03_P2.54mm_Vertical; Manufacturer Part Number PZ254V-11-03P; LCSC Part Number C2937625
JP12: 1-Wire PullUp Enable; PinHeader_1x02_P2.54mm_Vertical; Manufacturer Part Number PZ254V-11-02P; LCSC Part Number C492401
R2: 4.7k; R_0603_1608Metric_Pad0.98x0.95mm_HandSolder; Manufacturer Part Number RC0603FR-074K7L; LCSC Part Number C99782
R50, R51: 10k; R_0603_1608Metric_Pad0.98x0.95mm_HandSolder; Manufacturer Part Number RC0603FR-0710KL; LCSC Part Number C98220

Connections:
3V3: D23.2 (A2), J5.3, J6.2, R2.1; also elsewhere on the board
ADC_REF: R50.2, R51.2; also elsewhere on the board
AGND: J16.1, J17.1; also elsewhere on the board
DC_IN: F1.2; also elsewhere on the board
DQ: D7.2 (A2), J5.2, JP12.2 (B); also elsewhere on the board
GND: D7.1 (A1), D8.1 (A1), D13.1 (A1), D14.1 (A1), D16.1 (A1), D17.1 (A1), D23.1 (A1), J1.2, J5.1, J6.1, J19.1; also elsewhere on the board
unnamed: D8.2 (A2), F1.1, J1.1
unnamed: JP12.1 (A), R2.2
RX: D17.2 (A2), J19.2; also elsewhere on the board
SCL: D14.2 (A2), J6.4; also elsewhere on the board
SDA: D13.2 (A2), J6.3; also elsewhere on the board
TEMP1_READ: J16.2, R50.1; also elsewhere on the board
TEMP2_READ: J17.2, R51.1; also elsewhere on the board
TX: D16.2 (A2), J19.3; also elsewhere on the board

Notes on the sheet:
Connectors / Sensors
DC Power Connector
Display Connectors

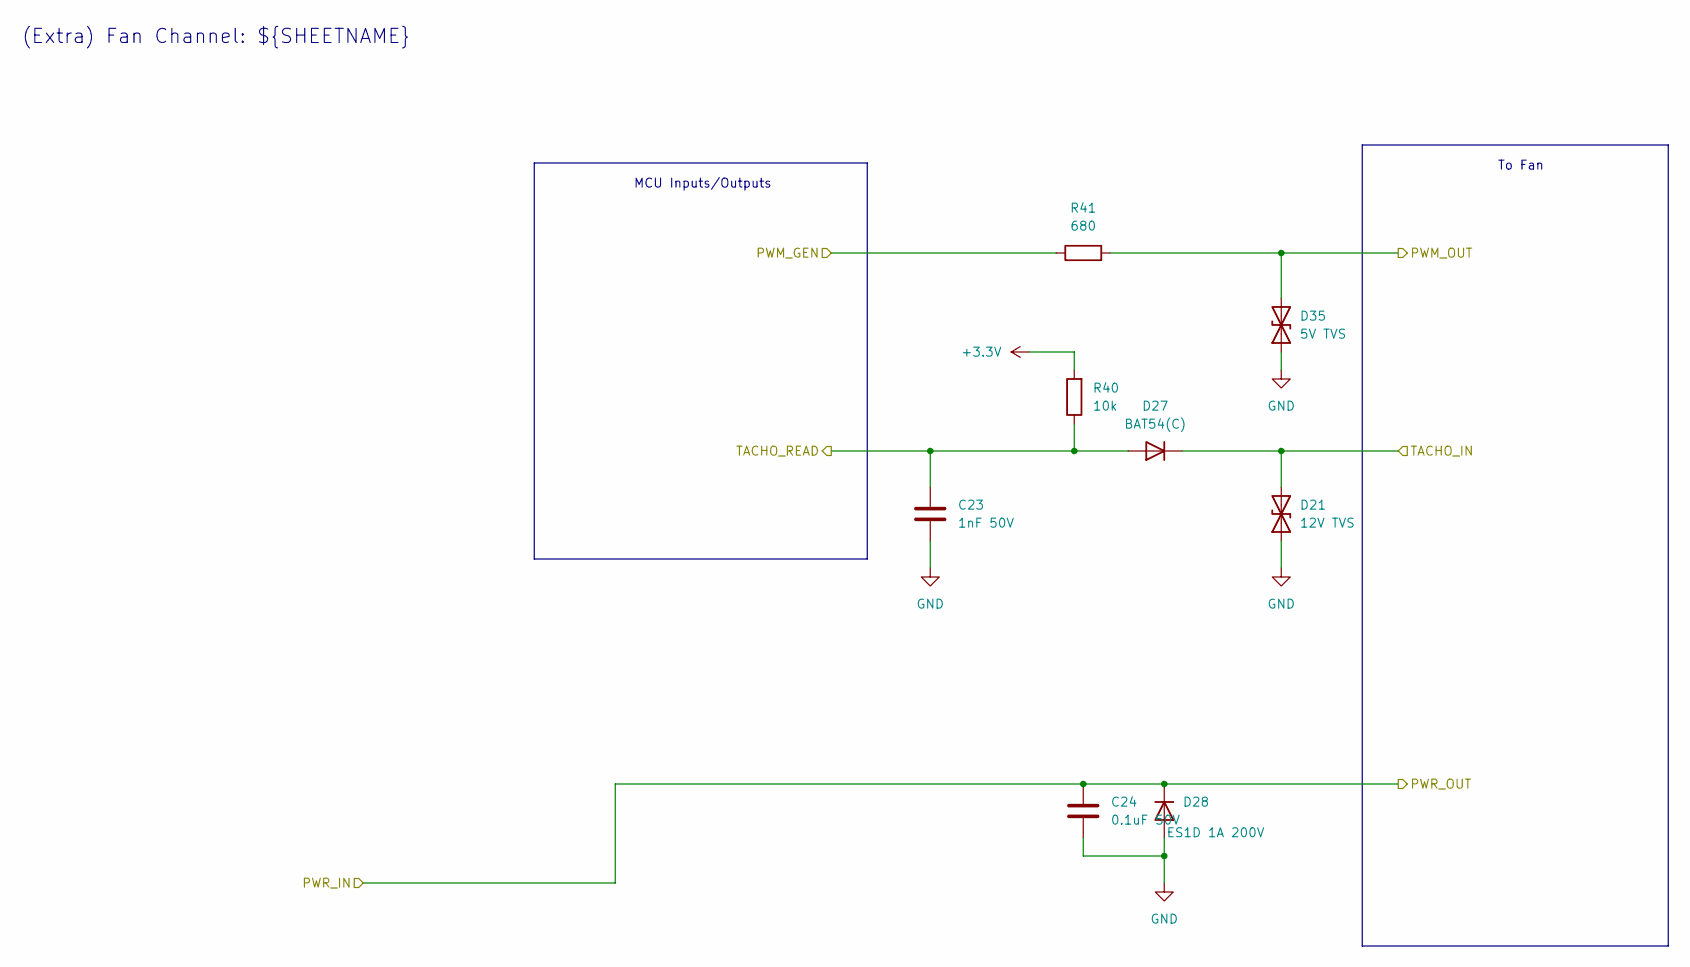
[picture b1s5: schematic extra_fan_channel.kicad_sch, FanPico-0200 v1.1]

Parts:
C23: 1nF 50V; C_0603_1608Metric_Pad1.08x0.95mm_HandSolder; Manufacturer Part Number CL10B102KB8NNNC; LCSC Part Number C1588
C24: 0.1uF 50V; C_0603_1608Metric_Pad1.08x0.95mm_HandSolder; Manufacturer Part Number CL10B104KB8NNNC; LCSC Part Number C1591
D21: 12V TVS; D_SOD-323_HandSoldering; Manufacturer Part Number UDD32C12L01-ES; LCSC Part Number C5199168
D27: BAT54(C); D_SOT-23_ANK; Mouser Part Number 241-BAT54C_R1_00001; LCSC Part Number C2844172
D28: ES1D 1A 200V; D_SMA_Handsoldering; Mouser Part Number 512-ES1D; LCSC Part Number C445494
D35: 5V TVS; D_SOD-323_HandSoldering; Manufacturer Part Number PESD5V0S1BA-ES; LCSC Part Number C5180216
R40: 10k; R_0603_1608Metric_Pad0.98x0.95mm_HandSolder; Manufacturer Part Number RC0603FR-0710KL; LCSC Part Number C98220
R41: 680; R_0603_1608Metric_Pad0.98x0.95mm_HandSolder; Manufacturer Part Number RC0603JR-07680RL; LCSC Part Number C115415

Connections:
3V3: R40.2; also elsewhere on the board
/Fan Channels/Fan1/PWM_OUT: D35.2 (A2), R41.2; also elsewhere on the board
/Fan Channels/Fan1/TACHO_IN: D21.2 (A2), D27.1 (K); also elsewhere on the board
FAN1_PWM_GEN: R41.1; also elsewhere on the board
FAN1_TACHO_READ: C23.1, D27.2 (A), R40.1; also elsewhere on the board
GND: C23.2, C24.2, D21.1 (A1), D28.2 (A), D35.1 (A1); also elsewhere on the board
MAIN_PWR: C24.1, D28.1 (K); also elsewhere on the board

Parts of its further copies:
C25: 1nF 50V; C_0603_1608Metric_Pad1.08x0.95mm_HandSolder; Manufacturer Part Number CL10B102KB8NNNC; LCSC Part Number C1588
C26: 0.1uF 50V; C_0603_1608Metric_Pad1.08x0.95mm_HandSolder; Manufacturer Part Number CL10B104KB8NNNC; LCSC Part Number C1591
D22: 12V TVS; D_SOD-323_HandSoldering; Manufacturer Part Number UDD32C12L01-ES; LCSC Part Number C5199168
D30: BAT54(C); D_SOT-23_ANK; Mouser Part Number 241-BAT54C_R1_00001; LCSC Part Number C2844172
D31: ES1D 1A 200V; D_SMA_Handsoldering; Mouser Part Number 512-ES1D; LCSC Part Number C445494
D36: 5V TVS; D_SOD-323_HandSoldering; Manufacturer Part Number PESD5V0S1BA-ES; LCSC Part Number C5180216
R43: 10k; R_0603_1608Metric_Pad0.98x0.95mm_HandSolder; Manufacturer Part Number RC0603FR-0710KL; LCSC Part Number C98220
R44: 680; R_0603_1608Metric_Pad0.98x0.95mm_HandSolder; Manufacturer Part Number RC0603JR-07680RL; LCSC Part Number C115415

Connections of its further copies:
3V3: R43.2; also elsewhere on the board
/Fan Channels/Fan2/PWM_OUT: D36.2 (A2), R44.2; also elsewhere on the board
/Fan Channels/Fan2/TACHO_IN: D22.2 (A2), D30.1 (K); also elsewhere on the board
FAN2_PWM_GEN: R44.1; also elsewhere on the board
FAN2_TACHO_READ: C25.1, D30.2 (A), R43.1; also elsewhere on the board
GND: C25.2, C26.2, D22.1 (A1), D31.2 (A), D36.1 (A1); also elsewhere on the board
MAIN_PWR: C26.1, D31.1 (K); also elsewhere on the board

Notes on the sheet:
MCU Inputs/Outputs
(Extra) Fan Channel: ${SHEETNAME}
To Fan
